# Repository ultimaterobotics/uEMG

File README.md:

# uEMG - 4-channel EMG device
This repository contains PCB design, firmware and PC program for analysing data (that one has hardly readable code for now, it's a work in progress with thousands lines of code dedicated to various signal processing approaches with only small part of them used in current version)

Firmware is in relatively good state. It depends on our nrf library: https://github.com/ultimaterobotics/urf_lib and requires bootloader: https://github.com/ultimaterobotics/uECG_bootloader

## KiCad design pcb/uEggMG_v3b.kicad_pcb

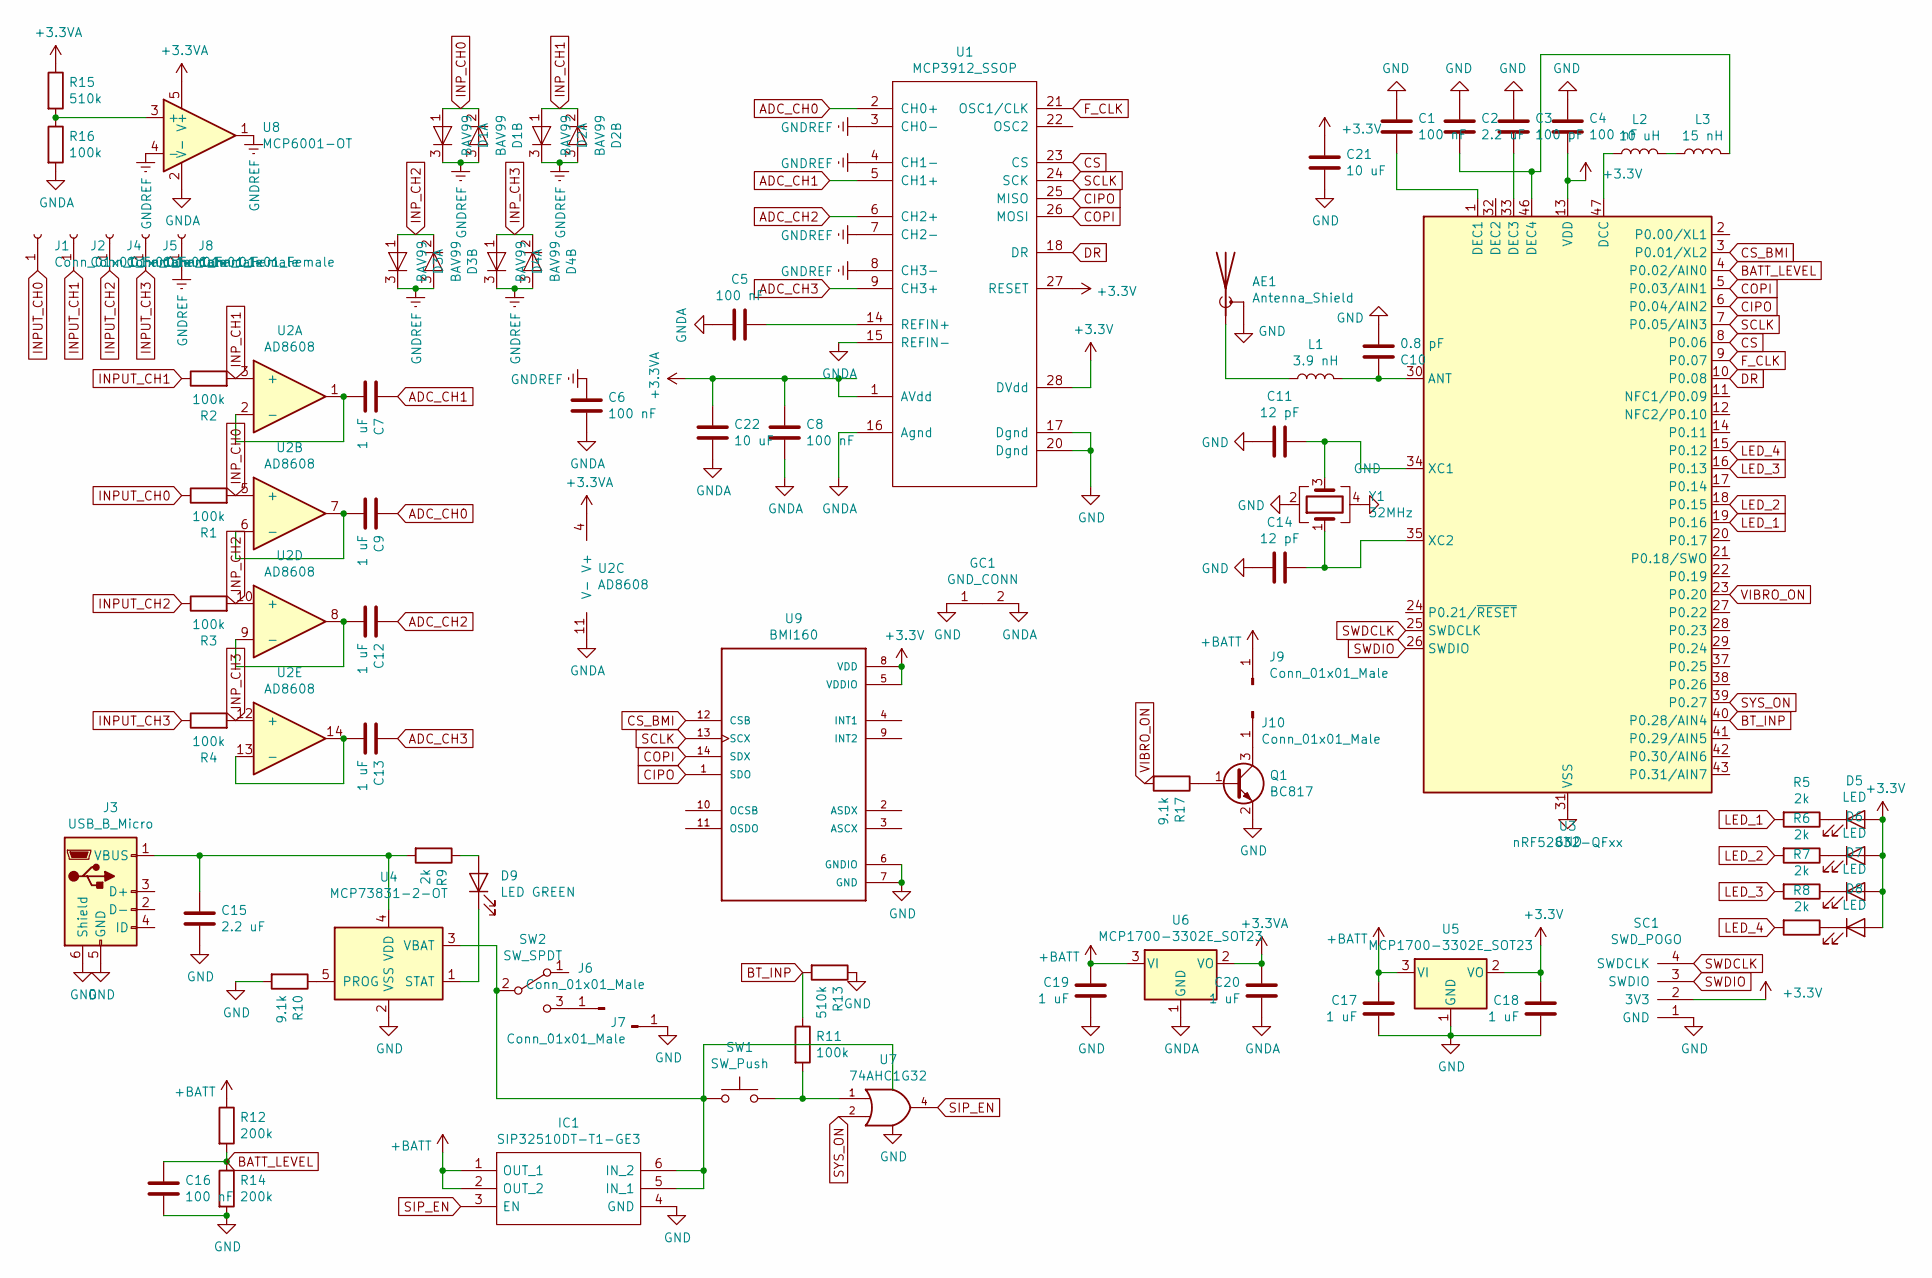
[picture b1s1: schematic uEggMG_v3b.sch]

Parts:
AE1: Antenna_Shield; U.FL_Hirose_U.FL-R-SMT-1_Vertical
C1, C4, C5, C6, C8, C16: 100 nF; C_0402_1005Metric
C2, C15: 2.2 uF; C_0402_1005Metric
C3: 100 pF; C_0402_1005Metric
C7, C9, C12, C13, C17, C18, C19, C20: 1 uF; C_0402_1005Metric
C10: 0.8 pF; C_0402_1005Metric
C11, C14: 12 pF; C_0402_1005Metric
C21, C22: 10 uF; C_0603_1608Metric
D1, D2, D3, D4: BAV99; SOT-23
D5, D6, D7, D8: LED; LED_0603_1608Metric
D9: LED GREEN; LED_0603_1608Metric
GC1: GND_CONN
IC1: SIP32510DT-T1-GE3; SOT95P284X110-6N; Manufacturer_Part_Number SIP32509DT-T1-GE3
J1, J2, J4, J5, J8: Conn_01x01_Female; textile_button_6mm
J3: USB_B_Micro; conn_usb_B_micro_smd_our
J6, J7, J9, J10: Conn_01x01_Male; PinHeader_1x01_P2.54mm_Vertical
L1: 3.9 nH; L_0402_1005Metric
L2: 10 uH; L_0603_1608Metric
L3: 15 nH; L_0402_1005Metric
Q1: BC817; SOT-23
R1, R2, R3, R4, R11, R16: 100k; R_0402_1005Metric
R5, R6, R7, R8, R9: 2k; R_0402_1005Metric
R10, R17: 9.1k; R_0402_1005Metric
R12, R14: 200k; R_0402_1005Metric
R13, R15: 510k; R_0402_1005Metric
SC1: SWD_POGO
SW1: SW_Push; BTN_HY_1185
SW2: SW_SPDT; SW_SPDT_PCM12
U1: MCP3912_SSOP; SSOP-28_5.3x10.2mm_P0.65mm
U2: AD8608; TSSOP-14_4.4x5mm_P0.65mm
U3: nRF52832-QFxx; QFN-48-1EP_6x6mm_Pitch0.4mm
U4: MCP73831-2-OT; SOT-23-5
U5, U6: MCP1700-3302E_SOT23; SOT-23
U7: 74AHC1G32; TSOT-23-5
U8: MCP6001-OT; SOT-23-5
U9: BMI160; PQFN50P300X250X88-14N
Y1: 32MHz; Crystal_SMD_2016-4Pin_2.0x1.6mm

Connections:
+3.3VA: C8.1, C20.2, C22.1, R15.1, U1.1 (AVdd), U2.4 (V+), U6.2 (VO), U8.5 (V+)
+3V3: C4.1, C18.2, C21.1, D5.2 (A), D6.2 (A), D7.2 (A), D8.2 (A), SC1.2 (3V3), U1.27 (RESET), U1.28 (DVdd), U3.13 (VDD), U3.36 (VDD), U3.48 (VDD), U5.2 (VO), U9.5 (VDDIO), U9.8 (VDD)
+BATT: C17.2, C19.2, IC1.1 (OUT_1), IC1.2 (OUT_2), J9.1, R12.1, U5.3 (VI), U6.3 (VI)
ADC_CH0: C9.1, U1.2 (CH0+)
ADC_CH1: C7.1, U1.5 (CH1+)
ADC_CH2: C12.1, U1.6 (CH2+)
ADC_CH3: C13.1, U1.9 (CH3+)
BATT_LEVEL: C16.2, R12.2, R14.1, U3.4 (P0.02/AIN0)
BT_INP: R11.1, R13.2, U3.40 (P0.28/AIN4)
CIPO: U1.25 (MISO), U3.6 (P0.04/AIN2), U9.1 (SDO)
COPI: U1.26 (MOSI), U3.5 (P0.03/AIN1), U9.14 (SDX)
CS: U1.23 (CS), U3.8 (P0.06)
CS_BMI: U3.3 (P0.01/XL2), U9.12 (CSB)
DR: U1.18 (DR), U3.10 (P0.08)
F_CLK: U1.21 (OSC1/CLK), U3.9 (P0.07)
GND: AE1.2 (Shield), C1.2, C2.2, C3.2, C4.2, C10.2, C11.1, C14.1, C15.1, C16.1, C17.1, C18.1, C19.1, C21.2, GC1.1, IC1.4 (GND), J3.5 (GND), J3.6 (Shield), J7.1, Q1.2 (E), R10.2, R13.1, R14.2, SC1.1 (GND), U1.17 (Dgnd), U1.20 (Dgnd), U3.31 (VSS), U3.45 (VSS), U3.49 (VSS), U4.2 (VSS), U5.1 (GND), U7.3 (GND), U9.6 (GNDIO), U9.7 (GND), Y1.2, Y1.4
GNDA: C5.2, C6.2, C8.2, C20.1, C22.2, GC1.2, R16.2, U1.10, U1.11, U1.12, U1.13, U1.15 (REFIN-), U1.16 (Agnd), U1.19, U2.11 (V-), U6.1 (GND), U8.2 (V-)
GNDREF: C6.1, D1.3 (K), D2.3 (K), D3.3 (K), D4.3 (K), J8.1, U1.3 (CH0-), U1.4 (CH1-), U1.7 (CH2-), U1.8 (CH3-), U8.1, U8.4 (-)
INPUT_CH0: J1.1, R1.1
INPUT_CH1: J2.1, R2.1
INPUT_CH2: J4.1, R3.1
INPUT_CH3: J5.1, R4.1
INP_CH0: D1.1 (A), D1.2 (K), R1.2, U2.5 (+)
INP_CH1: D2.1 (A), D2.2 (K), R2.2, U2.3 (+)
INP_CH2: D3.1 (A), D3.2 (K), R3.2, U2.10 (+)
INP_CH3: D4.1 (A), D4.2 (K), R4.2, U2.12 (+)
LED_1: R5.2, U3.19 (P0.16)
LED_2: R6.2, U3.18 (P0.15)
LED_3: R7.2, U3.16 (P0.13)
LED_4: R8.2, U3.15 (P0.12)
unnamed: AE1.1 (A), L1.1
unnamed: C1.1, U3.1 (DEC1)
unnamed: C2.1, L3.2, U3.46 (DEC4)
unnamed: C3.1, U3.33 (DEC3)
unnamed: C5.1, U1.14 (REFIN+)
unnamed: C7.2, U2.1, U2.2 (-)
unnamed: C9.2, U2.6 (-), U2.7
unnamed: C10.1, L1.2, U3.30 (ANT)
unnamed: C11.2, U3.34 (XC1), Y1.3
unnamed: C12.2, U2.8, U2.9 (-)
unnamed: C13.2, U2.13 (-), U2.14
unnamed: C14.2, U3.35 (XC2), Y1.1
unnamed: C15.2, J3.1 (VBUS), R9.2, U4.4 (VDD)
unnamed: D5.1 (K), R5.1
unnamed: D6.1 (K), R6.1
unnamed: D7.1 (K), R7.1
unnamed: D8.1 (K), R8.1
unnamed: D9.1 (K), U4.1 (STAT)
unnamed: D9.2 (A), R9.1
unnamed: J6.1, SW2.3 (C)
unnamed: J10.1, Q1.3 (C)
unnamed: L2.1, U3.47 (DCC)
unnamed: L2.2, L3.1
unnamed: Q1.1 (B), R17.1
unnamed: R10.1, U4.5 (PROG)
unnamed: R11.2, SW1.2, U7.1
unnamed: R15.2, R16.1, U8.3 (+)
SCLK: U1.24 (SCK), U3.7 (P0.05/AIN3), U9.13 (SCX)
SIP_EN: IC1.3 (EN), U7.4
SWDCLK: SC1.4 (SWDCLK), U3.25 (SWDCLK)
SWDIO: SC1.3 (SWDIO), U3.26 (SWDIO)
SYS_ON: U3.39 (P0.27), U7.2
VCC: IC1.5 (IN_1), IC1.6 (IN_2), SW1.1, SW2.2 (B), U4.3 (VBAT), U7.5 (VCC)
VIBRO_ON: R17.2, U3.23 (P0.20)

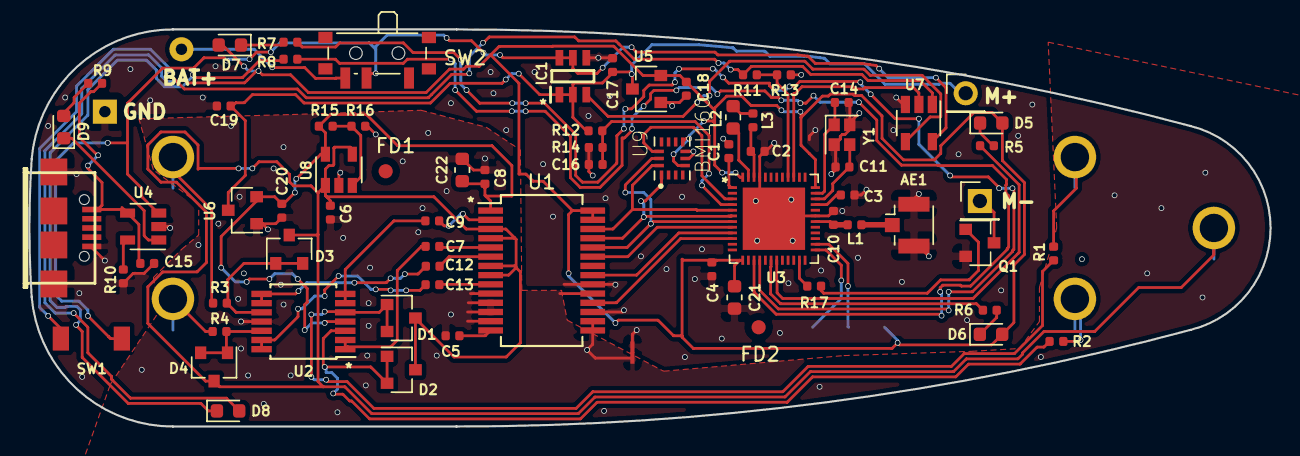
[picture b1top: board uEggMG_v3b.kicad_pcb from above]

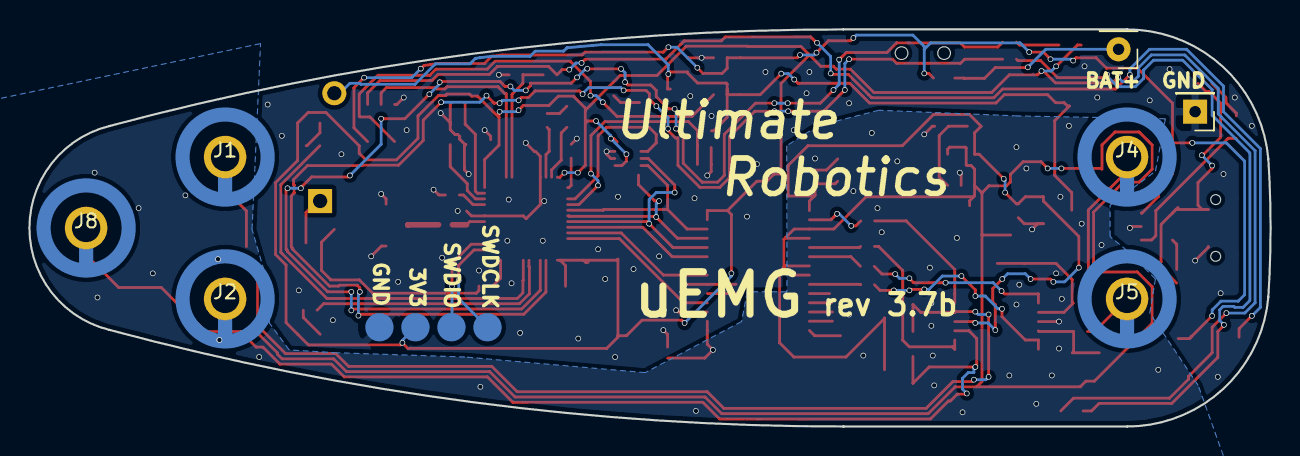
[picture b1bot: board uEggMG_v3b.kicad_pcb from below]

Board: 2 copper layers, 87.5 x 28.0 mm, 80 parts (8 on the bottom side), 64 nets.

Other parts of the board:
FD1, FD2: Fiducial_1mm_Dia_2mm_Outer

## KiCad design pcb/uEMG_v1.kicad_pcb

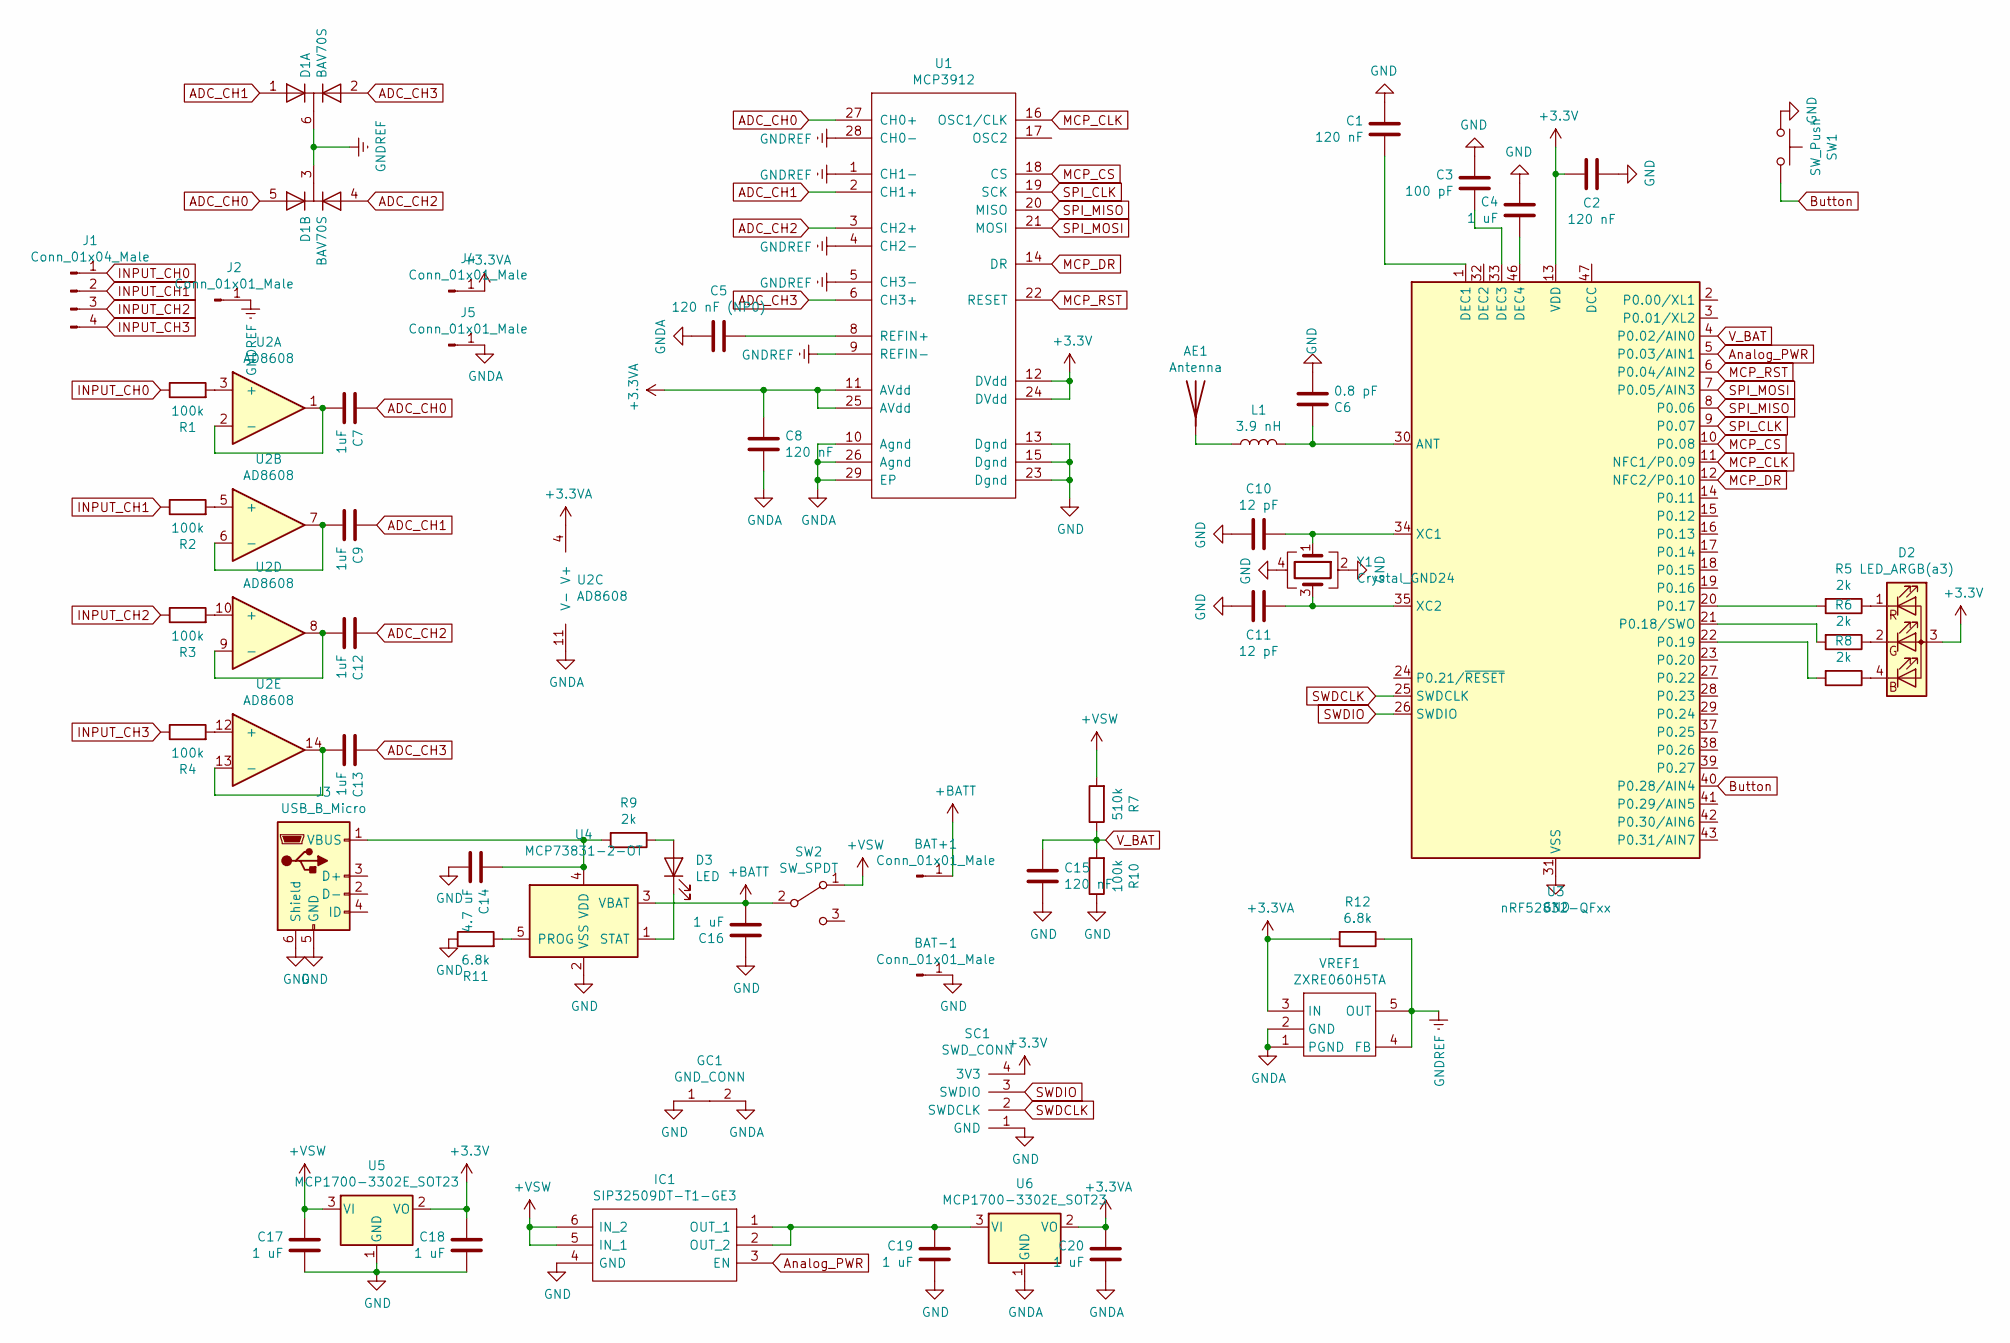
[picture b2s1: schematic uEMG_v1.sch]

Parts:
AE1: Antenna; Texas_SWRA117D_2.4GHz_Right
BAT+1: Conn_01x01_Male; PinHeader_1x01_P2.54mm_Vertical
BAT-1: Conn_01x01_Male; PinHeader_1x01_P2.54mm_Vertical
C1, C2, C8, C15: 120 nF; C_0402_1005Metric
C3: 100 pF; C_0402_1005Metric
C4, C16, C17, C18, C19, C20: 1 uF; C_0402_1005Metric
C5: 120 nF (NP0); C_0402_1005Metric
C6: 0.8 pF; C_0402_1005Metric
C7, C9, C12, C13: 1uF; C_0402_1005Metric
C10, C11: 12 pF; C_0402_1005Metric
C14: 4.7 uF; C_0402_1005Metric
D1: BAV70S; SOT-363_SC-70-6
D2: LED_ARGB(a3); LED_RGB_0603
D3: LED; LED_0603_1608Metric
GC1: GND_CONN
IC1: SIP32509DT-T1-GE3; SOT95P284X110-6N; Manufacturer_Part_Number SIP32509DT-T1-GE3
J1: Conn_01x04_Male; CONN_4_2.54
J2, J4, J5: Conn_01x01_Male; CONN_1_2.54
J3: USB_B_Micro; conn_usb_B_micro_smd_our
L1: 3.9 nH; L_0402_1005Metric
R1, R2, R3, R4, R10: 100k; R_0402_1005Metric
R5, R6, R8, R9: 2k; R_0402_1005Metric
R7: 510k; R_0402_1005Metric
R11, R12: 6.8k; R_0402_1005Metric
SC1: SWD_CONN; SWD_CONNECTOR
SW1: SW_Push; SW_SPST_B3U-1000P
SW2: SW_SPDT; Slider_Switch_ali
U1: MCP3912; QFN-28-1EP_5x5mm_P0.5mm_EP3.35x3.35mm
U2: AD8608; TSSOP-14_4.4x5mm_P0.65mm
U3: nRF52832-QFxx; QFN-48-1EP_6x6mm_Pitch0.4mm
U4: MCP73831-2-OT; SOT-23-5
U5, U6: MCP1700-3302E_SOT23; SOT-23
VREF1: ZXRE060H5TA; SOT-353_SC-70-5
Y1: Crystal_GND24; Crystal_SMD_2520-4pin_2.5x2.0mm

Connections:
+3.3VA: C8.1, C20.2, J4.1, R12.2, U1.11 (AVdd), U1.25 (AVdd), U2.4 (V+), U6.2 (VO), VREF1.3 (IN)
+3V3: C2.2, C18.2, D2.3 (A), SC1.4 (3V3), U1.12 (DVdd), U1.24 (DVdd), U3.13 (VDD), U3.36 (VDD), U3.48 (VDD), U5.2 (VO)
+BATT: BAT+1.1, C16.2, SW2.2 (B), U4.3 (VBAT)
+VSW: C17.2, IC1.5 (IN_1), IC1.6 (IN_2), R7.2, SW2.1 (A), U5.3 (VI)
ADC_CH0: C7.1, D1.5 (A), U1.27 (CH0+)
ADC_CH1: C9.1, D1.1 (A), U1.2 (CH1+)
ADC_CH2: C12.1, D1.4 (A), U1.3 (CH2+)
ADC_CH3: C13.1, D1.2 (A), U1.6 (CH3+)
Analog_PWR: IC1.3 (EN), U3.5 (P0.03/AIN1)
Button: SW1.2, U3.40 (P0.28/AIN4)
GND: AE1.2, BAT-1.1, C1.2, C2.1, C3.2, C4.2, C6.1, C10.2, C11.2, C14.2, C15.2, C16.1, C17.1, C18.1, C19.1, GC1.1, IC1.4 (GND), J3.5 (GND), J3.6 (Shield), R10.1, R11.1, SC1.1 (GND), SW1.1, U1.13 (Dgnd), U1.15 (Dgnd), U1.23 (Dgnd), U3.31 (VSS), U3.45 (VSS), U3.49 (VSS), U4.2 (VSS), U5.1 (GND), Y1.2, Y1.4
GNDA: C5.2, C8.2, C20.1, GC1.2, J5.1, U1.10 (Agnd), U1.26 (Agnd), U1.29 (EP), U2.11 (V-), U6.1 (GND), VREF1.1 (PGND), VREF1.2 (GND)
GNDREF: D1.3 (K), D1.6 (K), J2.1, R12.1, U1.1 (CH1-), U1.4 (CH2-), U1.5 (CH3-), U1.9 (REFIN-), U1.28 (CH0-), VREF1.4 (FB), VREF1.5 (OUT)
INPUT_CH0: J1.1, R1.1
INPUT_CH1: J1.2, R2.1
INPUT_CH2: J1.3, R3.1
INPUT_CH3: J1.4, R4.1
MCP_CLK: U1.16 (OSC1/CLK), U3.11 (NFC1/P0.09)
MCP_CS: U1.18 (CS), U3.10 (P0.08)
MCP_DR: U1.14 (DR), U3.12 (NFC2/P0.10)
MCP_RST: U1.22 (RESET), U3.6 (P0.04/AIN2)
unnamed: AE1.1, L1.1
unnamed: C1.1, U3.1 (DEC1)
unnamed: C3.1, U3.33 (DEC3)
unnamed: C4.1, U3.46 (DEC4)
unnamed: C5.1, U1.8 (REFIN+)
unnamed: C6.2, L1.2, U3.30 (ANT)
unnamed: C7.2, U2.1, U2.2 (-)
unnamed: C9.2, U2.6 (-), U2.7
unnamed: C10.1, U3.34 (XC1), Y1.1
unnamed: C11.1, U3.35 (XC2), Y1.3
unnamed: C12.2, U2.8, U2.9 (-)
unnamed: C13.2, U2.13 (-), U2.14
unnamed: C14.1, J3.1 (VBUS), R9.2, U4.4 (VDD)
unnamed: C19.2, IC1.1 (OUT_1), IC1.2 (OUT_2), U6.3 (VI)
unnamed: D2.1 (RK), R5.1
unnamed: D2.2 (GK), R6.1
unnamed: D2.4 (BK), R8.1
unnamed: D3.1 (K), U4.1 (STAT)
unnamed: D3.2 (A), R9.1
unnamed: R1.2, U2.3 (+)
unnamed: R2.2, U2.5 (+)
unnamed: R3.2, U2.10 (+)
unnamed: R4.2, U2.12 (+)
unnamed: R5.2, U3.20 (P0.17)
unnamed: R6.2, U3.21 (P0.18/SWO)
unnamed: R8.2, U3.22 (P0.19)
unnamed: R11.2, U4.5 (PROG)
SPI_CLK: U1.19 (SCK), U3.9 (P0.07)
SPI_MISO: U1.20 (MISO), U3.8 (P0.06)
SPI_MOSI: U1.21 (MOSI), U3.7 (P0.05/AIN3)
SWDCLK: SC1.2 (SWDCLK), U3.25 (SWDCLK)
SWDIO: SC1.3 (SWDIO), U3.26 (SWDIO)
V_BAT: C15.1, R7.1, R10.2, U3.4 (P0.02/AIN0)

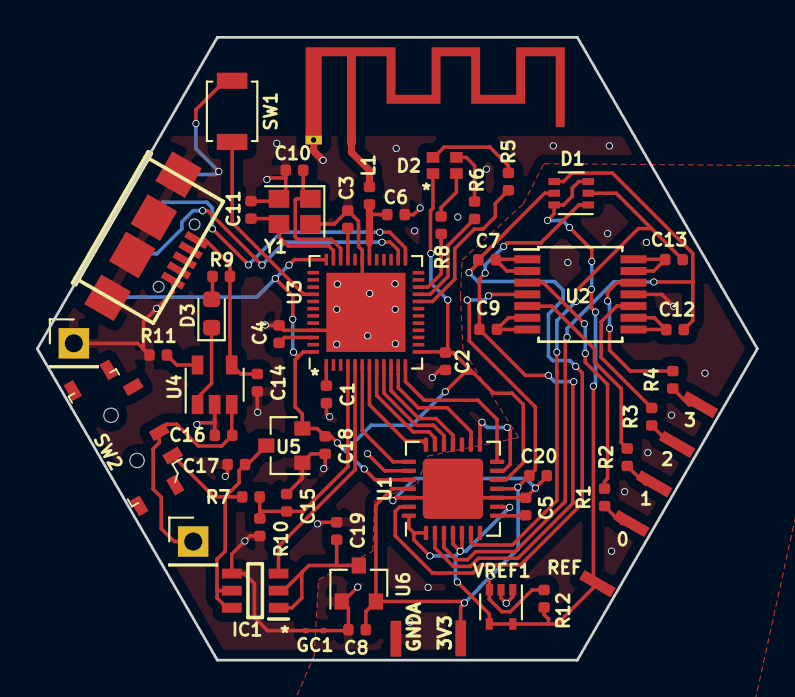
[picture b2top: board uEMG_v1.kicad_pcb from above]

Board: 2 copper layers, 40.0 x 34.6 mm, 57 parts (1 on the bottom side), 54 nets.

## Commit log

2020-06-19 v1 pcb design
2021-10-27 complete new versionuploaded, replacing old PCB and adding firmware, PC code
2021-10-27 updated description
